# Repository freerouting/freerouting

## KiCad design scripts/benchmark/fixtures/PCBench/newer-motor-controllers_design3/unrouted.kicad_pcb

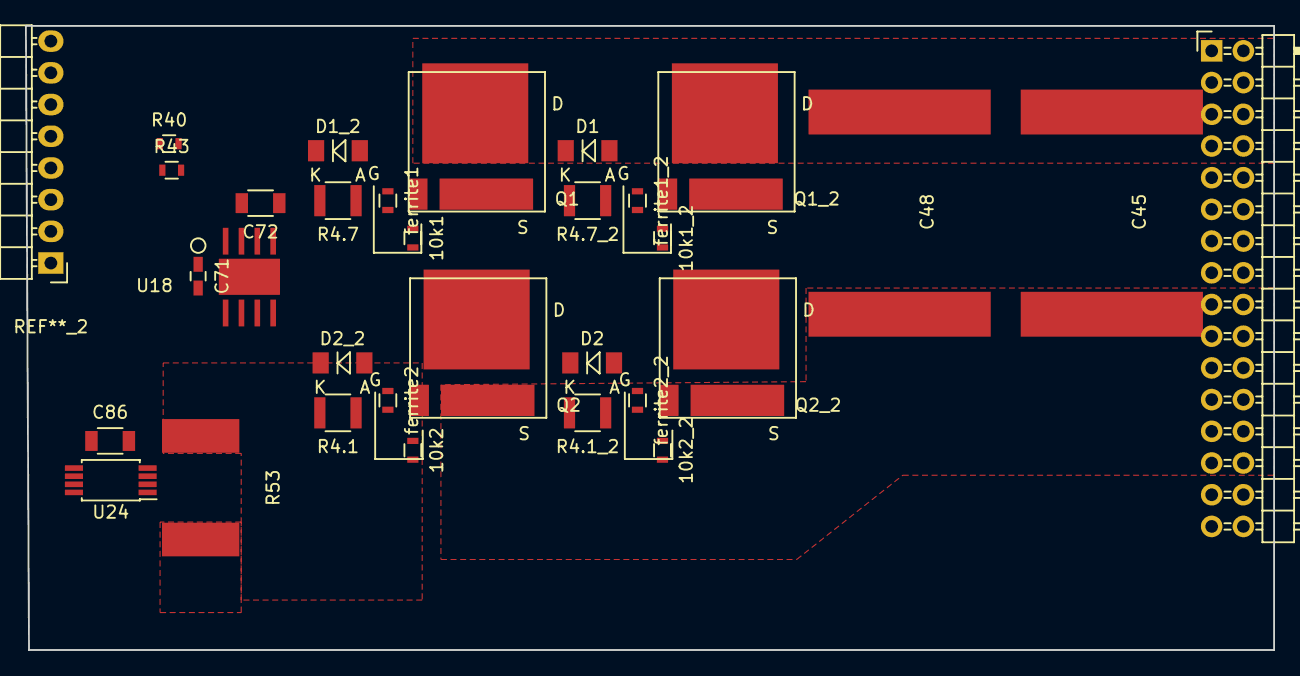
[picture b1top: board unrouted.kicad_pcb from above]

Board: 4 copper layers, 100.0 x 50.0 mm, 30 parts (0 on the bottom side), 14 nets, no tracks yet.

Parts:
10k1, 10k1_2, 10k2, 10k2_2: R_Small; R_0603
C45, C48: 4.7uf; cap_6065
C71: 1uf; C_0603_HandSoldering
C72, C86: 0.1uf; C_1206
D1, D1_2, D2, D2_2: D_Schottky_Small; MiniMELF_Standard
Q1, Q1_2, Q2, Q2_2: FDMT-800; P-PG-HSOF-08
R4.1, R4.1_2, R4.7, R4.7_2: R_Small; R_1210
R40: 1.8K; R_0603
R43: 39K; R_0603
R53: 0.001R; SHUNT_CSS2H-3920
U18: UCC27210; SO_PowerPAD-8
U24: INA240; TSSOP-8_4.4x3mm_Pitch0.65mm
ferrite1, ferrite1_2, ferrite2, ferrite2_2: R_Small; R_0603

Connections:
/Ti_120vgate/H1: D1.1, D1_2.1, R4.7.2, R4.7_2.2, U18.3
/Ti_120vgate/L1: D2.1, D2_2.1, R4.1.2, R4.1_2.2, U18.8
/Ti_120vgate/phase_a_in: 10k1.2, 10k1_2.2, C72.1, Q1.2, Q1_2.2, Q2.1, Q2_2.1, R43.1, R53.2, U18.4, U24.2
/connector/Vsense_a: R40.2, R43.2
/mosfet/VBUS: C45.2, C48.2, Q1.1, Q1_2.1
GND: 10k2.2, 10k2_2.2, C45.1, C48.1, C71.2, C86.2, Q2.2, Q2_2.2, R40.1, U18.7, U24.4, U24.7
unnamed: 10k1.1, 10k1_2.1, Q1.3, Q1_2.3, ferrite1.1, ferrite1_2.1
unnamed: 10k2.1, 10k2_2.1, Q2.3, Q2_2.3, ferrite2.1, ferrite2_2.1
unnamed: C71.1, U18.1
unnamed: C72.2, U18.2
unnamed: C86.1, U24.5, U24.6
unnamed: D1.2, D1_2.2, R4.7.1, R4.7_2.1, ferrite1.2, ferrite1_2.2
unnamed: D2.2, D2_2.2, R4.1.1, R4.1_2.1, ferrite2.2, ferrite2_2.2
unnamed: R53.1, U24.3

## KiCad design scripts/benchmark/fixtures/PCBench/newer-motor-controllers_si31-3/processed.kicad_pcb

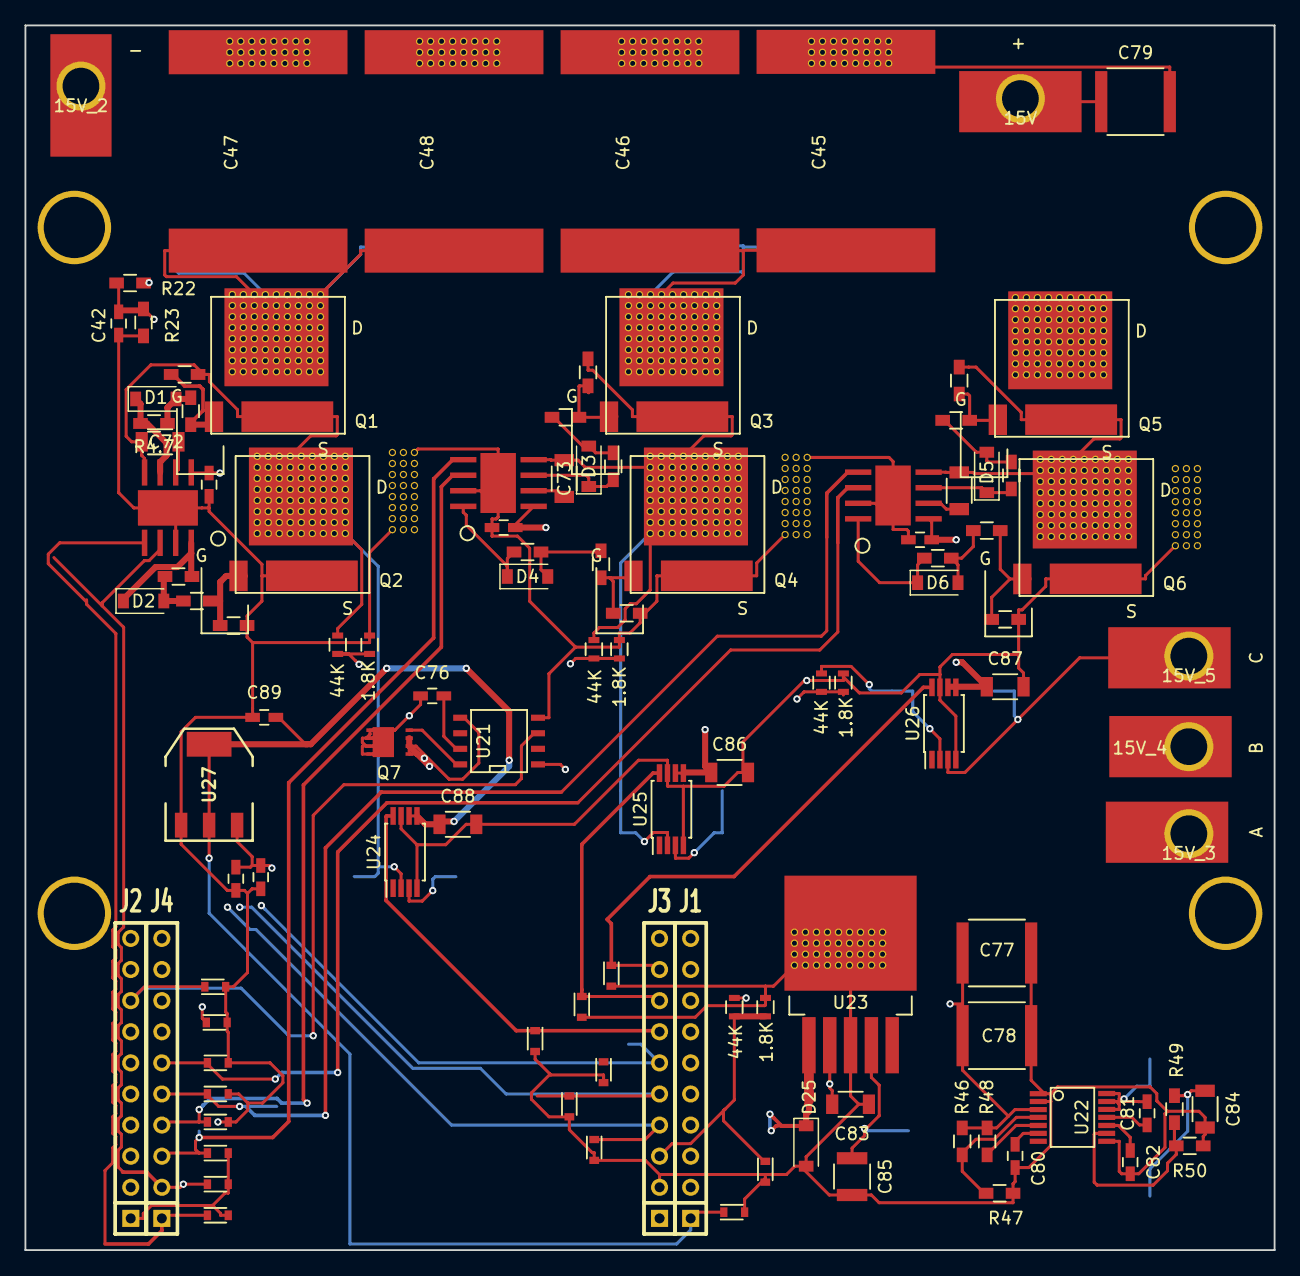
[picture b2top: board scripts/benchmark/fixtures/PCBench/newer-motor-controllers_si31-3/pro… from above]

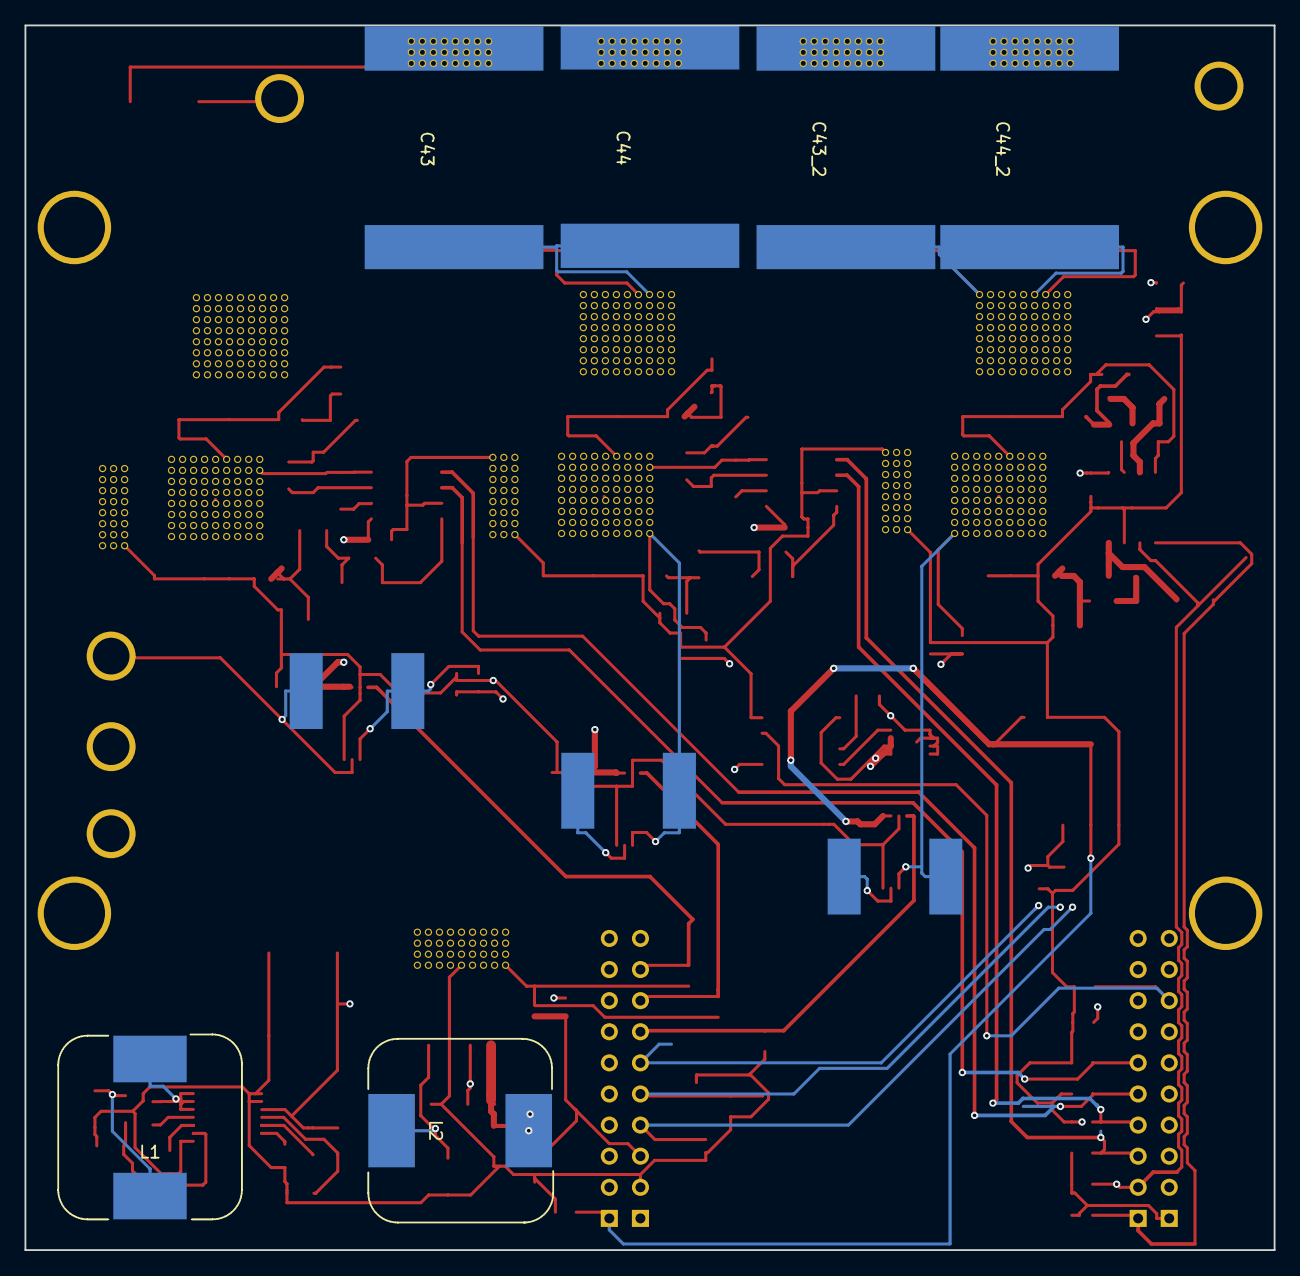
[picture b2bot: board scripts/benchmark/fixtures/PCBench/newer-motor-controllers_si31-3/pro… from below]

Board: 4 copper layers, 102.0 x 100.0 mm, 123 parts (9 on the bottom side), 58 nets.

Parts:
10k1, 10k2, 10k3, 10k4, 10k5, 10k6: R_Small; R_0603_HandSoldering
15V, 15V_2, 15V_3, 15V_4, 15V_5: via
+: V+; SolderWirePad_single_SMD_5x10mm
-: V-; SolderWirePad_single_SMD_5x10mm
A: motor_A; SolderWirePad_single_SMD_5x10mm
B: motor_B; SolderWirePad_single_SMD_5x10mm
C: motor_C; SolderWirePad_single_SMD_5x10mm
C42: 2.2uf; C_0603_HandSoldering
C43, C43_2, C44, C44_2, C45, C46, C47, C48: 4.7uf; cap_6065
C69, C70, C71, C82, C89: 1uf; C_0603_HandSoldering
C72, C73, C74, C86, C87, C88: 0.1uf; C_1206
C75: 0.1uf; C_0603_HandSoldering
C76: 10pf; C_0603_HandSoldering
C77, C78, C79: 1uf 250V; C_2220
C80: 22nf; C_0603_HandSoldering
C81: 10nf; C_0603_HandSoldering
C83, C84: 10uf; C_1206
C85: 100uf; C_1210
C90: 10uf; C_0603_HandSoldering
D1, D2, D3, D4, D5, D6: D_Schottky_Small; SOD-123
D8, D9, D10, D11, D12, D13, D14, D15, D16, D17, D18, D19, D20, D21, D22, D23: TVS; D_0603
D25: D_Schottky; SOD-123
J1: Ti_Booster_40_J1; SIL-10J1
J2: Ti_Booster_40_J2; SIL-10J2
J3: Ti_Booster_40_J3; SIL-10J3
J4: Ti_Booster_40_J4; SIL-10J4
L1, L2: INDUCTOR; MSS1583-154KED
Q1, Q2, Q3, Q4, Q5, Q6: FDMT-800; P-PG-HSOF-08
Q7: Q_NMOS_DSG; VSONP-8
R4.1, R4.2, R4.3, R4.4, R4.5, R4.7: R_Small; R_0603_HandSoldering
R22: NTC 10k; R_0603_HandSoldering
R23: 10k; R_0603_HandSoldering
R40, R41, R42, R42_2: 1.8K; R_0603
R43, R44, R45, R45_2: 44K; R_0603
R46: 75k; R_0603_HandSoldering
R47: 4.42k; R_0603_HandSoldering
R48: 499k; R_0603_HandSoldering
R49: 13k; R_0603_HandSoldering
R50: 2k; R_0603_HandSoldering
R51, R52, R53: 0.001R; SHUNT_CSS2H-3920
U18, U19, U20: UCC27210; SO_PowerPAD-8
U21: Si8751; SOIC-8-N
U22: LM5161; SSOP-14
U23: LM2595; TO-263-5Lead
U24, U25, U26: INA240; TSSOP-8_4.4x3mm_Pitch0.65mm
U27: NCP1117ST33T3G; SOT-223
ferrite1, ferrite2, ferrite3, ferrite4, ferrite5, ferrite6: R_Small; R_0603_HandSoldering

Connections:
+5V: C75.1, C85.1, C90.1, J3.1, L2.2, U21.1, U23.4, U27.3
+15V: C76.1, C83.1, C84.1, L1.2, Q7.1, R49.1, U23.2
/Ti_120vgate/vsense_a: D12.1, J3.4, R40.2, R43.2
/Ti_120vgate/vsense_b: D13.1, J3.5, R41.2, R44.2
/Ti_120vgate/vsense_c: J3.6, R42.2, R45.2
/VBUS: 15V.1, +.1, C43.2, C43_2.2, C44.2, C44_2.2, C45.2, C46.2, C47.2, C48.2, C77.1, C78.1, C79.1, Q1.1, Q3.1, Q5.1, R45_2.1, R46.1, R48.2, U22.3
/connector/CurrentA: D15.1, J3.7, U24.8
/connector/CurrentB: D16.1, J3.8, U25.8
/connector/CurrentC: D17.1, J3.9, U26.8
/connector/EN_GATE: D10.1, J2.8, U21.3
/connector/PWM_H1: D18.1, J4.1, U18.5
/connector/PWM_H2: D20.1, J4.3, U19.5
/connector/PWM_H3: D22.1, J4.5, U20.5
/connector/PWM_L1: D19.1, J4.2, U18.6
/connector/PWM_L2: D21.1, J4.4, U19.6
/connector/PWM_L3: D23.1, J4.6, U20.6
/connector/TEMP: C42.1, D8.1, J2.3, R22.2, R23.1
/connector/VBUS_sense: D11.1, J3.3, R42_2.2, R45_2.2
/current_sense_80v/PHASE_1: 15V_3.1, A.1, R53.1, U24.3
/current_sense_80v/PHASE_2: 15V_4.1, B.1, R52.1, U25.3
/current_sense_80v/PHASE_3: 15V_5.1, C.1, R51.1, U26.3
/mosfet/H1: D1.1, R4.7.2, U18.3
/mosfet/H2: D3.1, R4.2.2, U19.3
/mosfet/H3: D5.1, R4.4.2, U20.3
/mosfet/L1: D2.1, R4.1.2, U18.8
/mosfet/L2: D4.1, R4.3.2, U19.8
/mosfet/L3: D6.1, R4.5.2, U20.8
/mosfet/phase_a_in: 10k1.2, C72.1, Q1.2, Q2.1, R43.1, R53.2, U18.4, U24.2
/mosfet/phase_b_in: 10k3.2, C73.1, Q3.2, Q4.1, R44.1, R52.2, U19.4, U25.2
/mosfet/phase_c_in: 10k5.2, C74.1, Q5.2, Q6.1, R45.1, R51.2, U20.4, U26.2
GND: 10k2.2, 10k4.2, 10k6.2, 15V_2.1, -.1, C42.2, C43.1, C43_2.1, C44.1, C44_2.1, C45.1, C46.1, C47.1, C48.1, C69.2, C70.2, C71.2, C75.2, C77.2, C78.2, C79.2, C80.2, C82.2, C83.2, C84.2, C85.2, C86.2, C87.2, C88.2, C89.2, C90.2, D8.2, D9.2, D10.2, D11.2, D12.2, D13.2, D14.2, D15.2, D16.2, D17.2, D18.2, D19.2, D20.2, D21.2, D22.2, D23.2, D25.2, J2.1, J3.2, Q2.2, Q4.2, Q6.2, R23.2, R40.1, R41.1, R42.1, R42_2.1, R47.2, R50.2, U18.7, U18.pad, U19.7, U19.pad, U20.7, U20.pad, U21.4, U22.1, U22.2, U22.8, U23.3, U24.4, U24.7, U25.4, U25.7, U26.4, U26.7, U27.1
unnamed: 10k1.1, Q1.3, ferrite1.1
unnamed: 10k2.1, Q2.3, ferrite2.1
unnamed: 10k3.1, Q3.3, ferrite3.1
unnamed: 10k4.1, Q4.3, ferrite4.1
unnamed: 10k5.1, Q5.3, ferrite5.1
unnamed: 10k6.1, Q6.3, ferrite6.1
unnamed: C69.1, C70.1, C71.1, Q7.2, U18.1, U19.1, U20.1, U21.5
unnamed: C72.2, U18.2
unnamed: C73.2, U19.2
unnamed: C74.2, U20.2
unnamed: C76.2, U21.7
unnamed: C80.1, U22.6
unnamed: C81.1, L1.1, U22.12, U22.13, U22.14
unnamed: C81.2, U22.11
unnamed: C82.1, U22.10
unnamed: C86.1, C87.1, C88.1, C89.1, D9.1, J1.1, R22.1, U24.5, U24.6, U25.5, U25.6, U26.5, U26.6, U27.2
unnamed: D1.2, R4.7.1, ferrite1.2
unnamed: D2.2, R4.1.1, ferrite2.2
unnamed: D3.2, R4.2.1, ferrite3.2
unnamed: D4.2, R4.3.1, ferrite4.2
unnamed: D5.2, R4.4.1, ferrite5.2
unnamed: D6.2, R4.5.1, ferrite6.2
unnamed: D25.1, L2.1, U23.1
unnamed: Q7.3, U21.8
unnamed: R46.2, R47.1, U22.4
unnamed: R48.1, U22.5
unnamed: R49.2, R50.1, U22.9

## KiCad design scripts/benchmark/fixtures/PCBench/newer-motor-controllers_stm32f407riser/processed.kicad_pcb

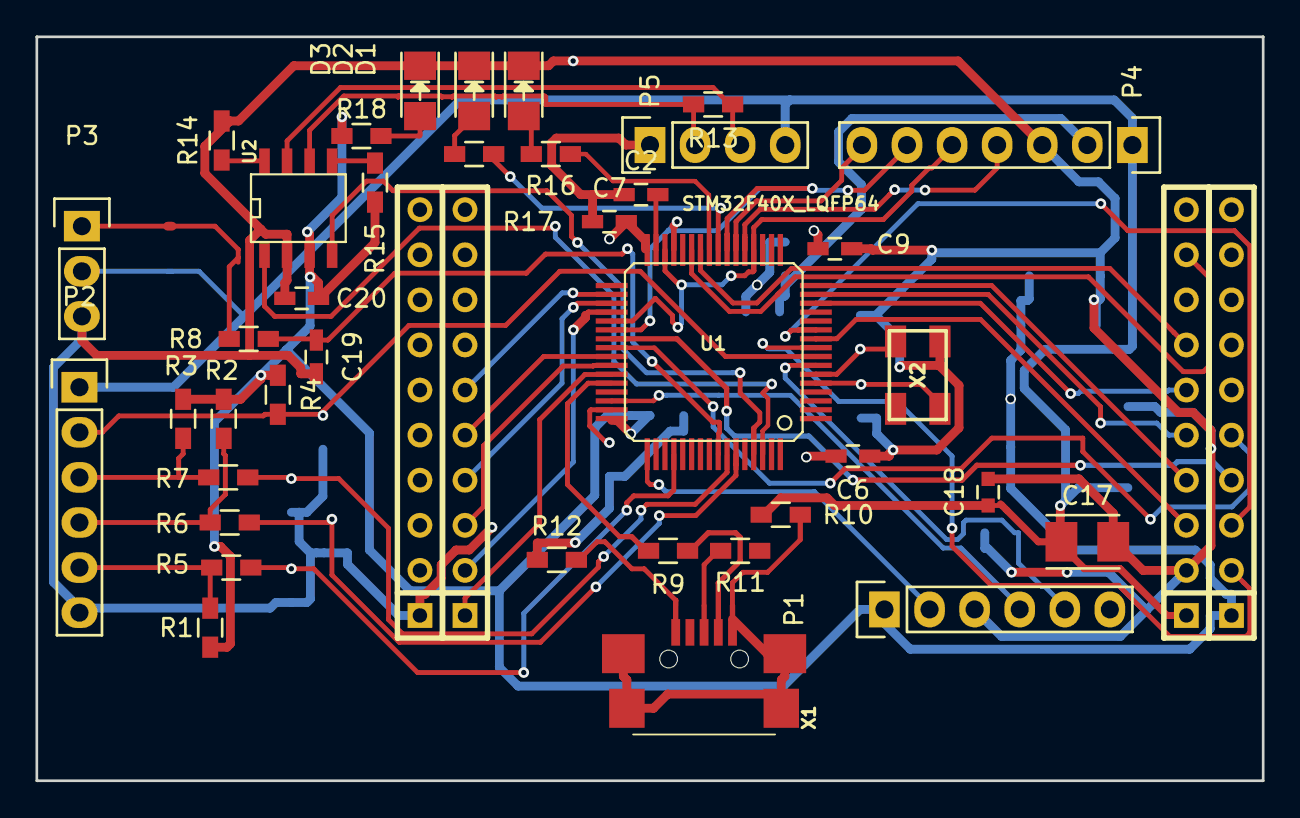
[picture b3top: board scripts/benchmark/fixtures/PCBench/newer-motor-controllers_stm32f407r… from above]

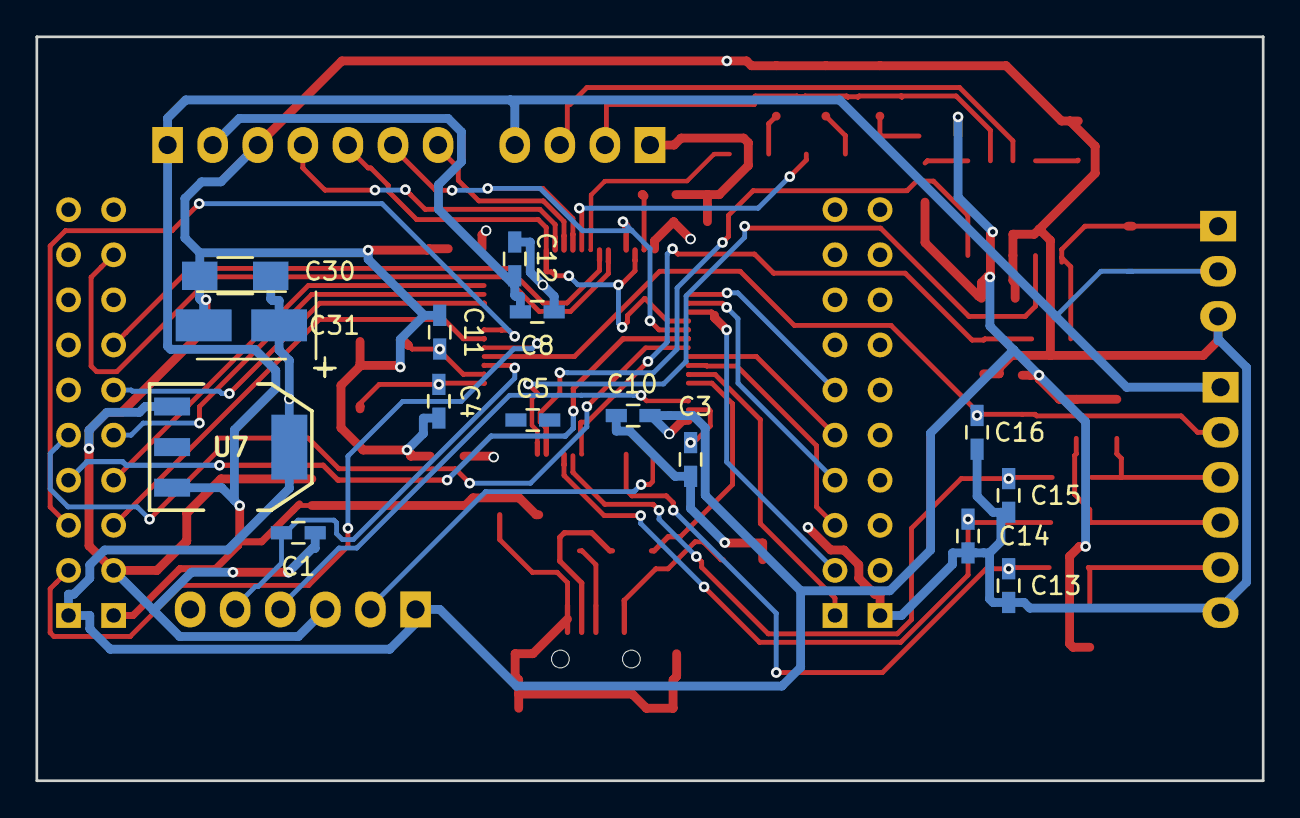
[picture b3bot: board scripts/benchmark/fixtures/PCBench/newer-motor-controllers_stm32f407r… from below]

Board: 4 copper layers, 69.1 x 41.9 mm, 57 parts (15 on the bottom side), 55 nets.

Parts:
C1: 100pf; C_0603_HandSoldering
C2, C3, C5, C6, C7, C8, C9, C10, C12, C20: 2.2uf; C_0603_HandSoldering
C4, C11: 15pf; C_0603_HandSoldering
C13, C14, C15, C16: 4.7nf; C_0603_HandSoldering
C17: 100uf; TantalC_SizeB_EIA-3528_Reflow
C18: 10uf; C_0603
C19: 100nf; C_0603_HandSoldering
C30: 2.2uf; C_1206_HandSoldering
C31: 100uf; TantalC_SizeB_EIA-3528_HandSoldering
D1, D2, D3: LED; LED_1206
J1: Ti_Booster_40_J1; SIL-10J1
J2: Ti_Booster_40_J2; SIL-10J2
J3: Ti_Booster_40_J3; SIL-10J3
J4: Ti_Booster_40_J4; SIL-10J4
P1, P2: CONN_01X06; Pin_Header_Straight_1x06
P3: CONN_01X03; Pin_Header_Straight_1x03
P4: CONN_01X07; Pin_Header_Straight_1x07
P5: CONN_01X04; Pin_Header_Straight_1x04
R1, R2, R3, R8, R18: 2k; R_0603_HandSoldering
R4, R5, R6, R7, R14, R15: 10k; R_0603_HandSoldering
R9, R11: 20r; R_0603_HandSoldering
R10, R12: 0r; R_0603_HandSoldering
R13: 120R; R_0603_HandSoldering
R16, R17: 100r; R_0603_HandSoldering
U1: STM32F40X_LQFP64; lqfp64_pad_mod_hand
U2: MCP2551-I/SN; SOIC-8-W
U7: NCP1117ST33T3G; SOT-223
X1: MINI-USB-SCHIELD-32005-201; USB-UX60R-MB-5ST
X2: 8MHz 10ppm; Crystal_5x3mm

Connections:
+3V3: C6.2, C7.2, C8.2, C9.2, C10.1, C12.1, C20.1, C30.1, C31.1, J1.1, P1.1, P4.2, R1.1, R2.1, R3.1, R4.1, R15.1, R18.2, U1.32, U1.48, U2.3, U7.2
+5V: C17.1, C18.1, J3.1, P2.1, P3.2, P4.1, P5.4, R10.1, U7.3
/Power MOSFETS/CAN_RX: U1.61, U2.4
/Power MOSFETS/CAN_TX: U1.62, U2.1
/Power MOSFETS/CurrentA: J3.7, U1.26
/Power MOSFETS/CurrentC: J3.9, U1.27
/Power MOSFETS/H1: J4.1, U1.43
/Power MOSFETS/H2: J4.3, U1.42
/Power MOSFETS/H3: J4.5, U1.41
/Power MOSFETS/HALL_1: C15.1, R7.1, U1.58
/Power MOSFETS/HALL_2: C14.1, R6.1, U1.59
/Power MOSFETS/HALL_3: C13.1, R5.1, U1.52
/Power MOSFETS/L1: J4.2, U1.36
/Power MOSFETS/L2: J4.4, U1.35
/Power MOSFETS/L3: J4.6, U1.34
/Power MOSFETS/LED_GREEN: R16.2, U1.25
/Power MOSFETS/LED_RED: R17.2, U1.24
/Power MOSFETS/MISO_ADC_EXT: P4.7, U1.22
/Power MOSFETS/PC1: J1.2, U1.9
/Power MOSFETS/PC3: J1.3, U1.11
/Power MOSFETS/PC8: J1.4, U1.39
/Power MOSFETS/PC9: J1.5, U1.40
/Power MOSFETS/RX_SCL_MOSI: P4.6, U1.23, U1.29, U1.38
/Power MOSFETS/SCK_ADC_EX: P4.4, U1.21
/Power MOSFETS/SERVO: C19.2, R8.2, U1.57
/Power MOSFETS/TEMP_MOTOR: C16.1, P2.2, R4.2, U1.8
/Power MOSFETS/TX_SDA_NSS: P4.5, U1.20, U1.30, U1.37
/Power MOSFETS/USB_DM: R9.2, U1.44
/Power MOSFETS/VBUS_SENSE: J3.3, U1.10
/Power MOSFETS/V_SENSE1: J3.4, U1.16
/Power MOSFETS/V_SENSE2: J3.5, U1.15
/Power MOSFETS/V_SENSE3: J3.6, U1.14
GND: C1.1, C2.1, C3.1, C4.1, C6.1, C7.1, C8.1, C9.1, C10.2, C11.1, C12.2, C13.2, C14.2, C15.2, C16.2, C17.2, C18.2, C19.1, C20.2, C30.2, C31.2, D1.1, D2.1, D3.1, J2.1, J3.2, P1.3, P2.6, P3.3, P4.3, P5.1, R12.1, R14.2, U2.2, U7.1, X2.3
unnamed: C1.2, P1.5, U1.7
unnamed: C2.2, U1.31
unnamed: C3.2, U1.47
unnamed: C4.2, U1.5, X2.1
unnamed: C11.2, U1.6, X2.2
unnamed: D1.2, R16.1
unnamed: D2.2, R17.1
unnamed: D3.2, R18.1
unnamed: P1.2, U1.49
unnamed: P1.4, U1.46
unnamed: P2.3, R3.2, R7.2
unnamed: P2.4, R2.2, R6.2
unnamed: P2.5, R1.2, R5.2
unnamed: P3.1, R8.1
unnamed: P5.2, R13.2, U2.6
unnamed: P5.3, R13.1, U2.7
unnamed: R9.1, X1.2
unnamed: R10.2, X1.1, X1.5
unnamed: R11.1, X1.3
unnamed: R12.2, X1.5
unnamed: R14.1, U2.8
unnamed: R15.2, U2.5

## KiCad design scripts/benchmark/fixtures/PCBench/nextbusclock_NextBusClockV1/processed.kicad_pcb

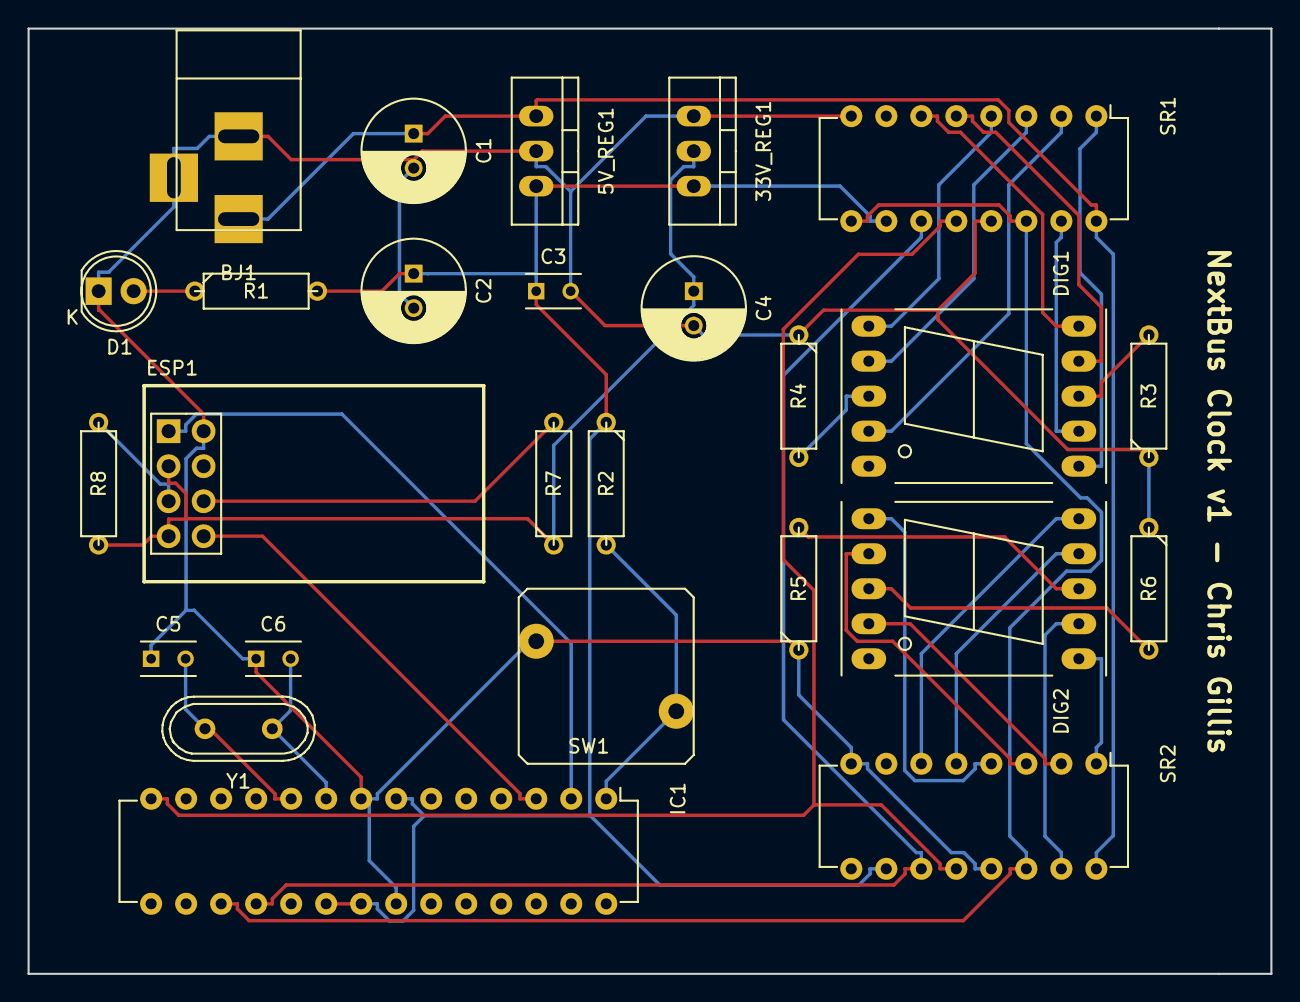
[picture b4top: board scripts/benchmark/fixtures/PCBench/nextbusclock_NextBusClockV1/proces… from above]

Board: 2 copper layers, 90.2 x 68.6 mm, 26 parts (0 on the bottom side), 33 nets.

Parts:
5V_REG1: LM7805; TO-220_Neutral123_Vertical
33V_REG1: LD1117V33; TO-220_Neutral123_Vertical
BJ1: BARREL_JACK
C1: 10uF; C_Radial_D7.5_L11.2_P2.5
C2: 1uF; C_Radial_D7.5_L11.2_P2.5
C3: 0.1uf; C_Rect_L4_W2.5_P2.5
C4: 10uf; C_Radial_D7.5_L11.2_P2.5
C5, C6: 22pF; C_Rect_L4_W2.5_P2.5
D1: PWR_LED; LED-5MM
DIG1, DIG2: LTS-6980HR; 7SegmentLED_LTS6760_LTS6780
ESP1: ESP-01
IC1: ATMEGA328-P; DIP-28_W7.62mm
R1: 1k; R3-5
R2, R7, R8: 10k; R3-5
R3, R4, R5, R6: 470; R3-5
SR1, SR2: 74HC595; DIP-16_W7.62mm
SW1: SW_PUSH
Y1: 16MHz; Crystal_HC49-U_Vertical

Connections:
/5V_PWR: 5V_REG1.3, 33V_REG1.3, C2.1, C3.1, IC1.7, IC1.20, IC1.21, R1.2, R2.1, SR1.10, SR2.10
/33V_PWR: 33V_REG1.2, C4.1, ESP1.3, ESP1.7, R7.1, R8.2
/ESP_RX: ESP1.8, IC1.3
/ESP_TX: ESP1.1, IC1.2
/SR_CLOCK: IC1.18, SR1.11, SR2.11
/SR_DATA: IC1.17, SR1.9, SR1.14, SR2.14
/SR_LATCH: IC1.14, SR1.12, SR2.12
GND: 5V_REG1.2, 33V_REG1.1, BJ1.2, BJ1.3, C1.2, C2.2, C3.2, C4.2, C5.1, C6.1, D1.1, ESP1.2, IC1.8, IC1.22, R3.1, R4.1, R5.1, R6.1, SR1.8, SR1.13, SR2.8, SR2.13, SW1.2
unnamed: C5.2, IC1.10, Y1.2
unnamed: C6.2, IC1.9, Y1.1
unnamed: D1.2, R1.1
unnamed: DIG1.1, SR1.4
unnamed: DIG1.2, SR1.3
unnamed: DIG1.3, R4.2
unnamed: DIG1.4, SR1.2
unnamed: DIG1.6, SR1.1
unnamed: DIG1.7, SR1.15
unnamed: DIG1.8, R3.2
unnamed: DIG1.9, SR1.5
unnamed: DIG1.10, SR1.6
unnamed: DIG2.1, SR2.4
unnamed: DIG2.2, SR2.3
unnamed: DIG2.3, R6.2
unnamed: DIG2.4, SR2.2
unnamed: DIG2.6, SR2.1
unnamed: DIG2.7, SR2.15
unnamed: DIG2.8, R5.2
unnamed: DIG2.9, SR2.5
unnamed: DIG2.10, SR2.6
unnamed: ESP1.5, R8.1
unnamed: ESP1.6, R7.2
unnamed: IC1.1, R2.2, SW1.1
VCC: 5V_REG1.1, BJ1.1, C1.1, SR1.16, SR2.16
